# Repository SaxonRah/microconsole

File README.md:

# MicroConsole

MicroConsole is a small cross-platform console integration project built around
[MicroRender](third_party/microrender) for graphics and
[MicroWave](third_party/microwave) for audio.

The repository does **not** fork either engine. MicroRender and MicroWave remain
pinned Git submodules; MicroConsole owns the platform glue that runs them at the
same time and is the place where console-level services can be added later.

The current program is deliberately a stress/integration demo rather than a
finished game runtime: the deterministic MicroRender stress scene runs
continuously while the MicroWave music demo plays.

## Validated baseline

As of **2026-09-01**, the combined integration is working on all three targets:

| Target | Graphics | Audio | Validated result |
| --- | --- | --- | --- |
| Pico 2 / Pimoroni Pico Plus 2 | 320x240 RGB565 ILI9341, 1024-sprite 8-row lace | 32 kHz I2S | ~110 FPS with continuous audio |
| 16-bit DOS | 320x240 RGB565 logical image -> RGB332 Mode X | 11.025 kHz Sound Blaster 8-bit DMA | ~92 FPS with continuous audio |
| Raylib desktop | 320x240 RGB565, 1024-sprite 8-row lace | 32 kHz Raylib `AudioStream` | graphics + audio verified working |

The DOS reference/diagnostic builds measure 97 FPS (`MCREF`), 94 FPS
(`MCGFX`), and 95 FPS (`MCDEMO /noaudio`) for the same 1024-sprite workload,
which puts the combined 92 FPS result within a few percent of the renderer-only
baseline.

See [docs/VALIDATION.md](docs/VALIDATION.md) for the exact test commands and
what each number means.

## Quick start

Clone the repository, then initialize the pinned dependencies:

```powershell
.\mc.bat deps
```

### Raylib

```powershell
.\mc.bat build raylib
.\mc.bat run raylib
```

Press **Space** to trigger the MicroWave synth SFX while the music demo is
playing.

### DOS

```powershell
.\mc.bat build dos
.\mc.bat run dos /sprites 1024 /frames 2100
```

The DOS build also produces two renderer-parity diagnostics:

```powershell
.\mc.bat run dosref /sprites 1024 /frames 2100
.\mc.bat run dosgfx /sprites 1024 /frames 2100
.\mc.bat run dos /sprites 1024 /frames 2100 /noaudio
```

### Pico 2

```powershell
.\mc.bat build pico max98357a
.\mc.bat run pico max98357a swd
```

Other audio presets:

```powershell
.\mc.bat build pico pcm5102a
.\mc.bat build pico ns4168
```

Flash methods are `swd` (default), `picotool`, and `manual` BOOTSEL copy.

## Dependency pins

MicroConsole is validated against these exact engine revisions:

- MicroRender: `61d8d875cbdf605edaa2b6ca2f2e5739b80ee61d`
- MicroWave: `2492cc4026a5e3cdebbac6dea91dbc9eabe88d91`

`mc.bat deps` initializes those two gitlinks, checks out the pinned commits, and
initializes the single Raylib checkout nested under MicroRender. It can also
repair the specific case where `.gitmodules` survived a copied/archive tree but
the two mode-160000 gitlink entries did not.

## What belongs here

MicroConsole owns integration and platform policy:

- selecting/building the two engines together;
- display/audio device setup;
- platform scheduling between rendering, presentation, and mixing;
- console-facing input/storage/save/power services as they are added;
- target-specific diagnostics and performance regression tests.

MicroConsole does **not** own the renderer or mixer implementation. Changes that
are generally useful to graphics belong in MicroRender; changes generally useful
to audio belong in MicroWave.

## Repository layout

```text
microconsole/
  mc.bat                  one build/run/dependency entry point
  CMakeLists.txt          Raylib combined target
  pico/                   Pico SDK project and audio-device presets
  scripts/                build, run, flash/tooling helpers
  src/
    dos/                   DOS combined frontend + Sound Blaster transport
    pico/                  RP2350 combined frontend
    raylib/                desktop combined frontend
  docs/
    ARCHITECTURE.md        ownership, data flow, platform resource model
    BUILDING.md            prerequisites and exact build/run options
    VALIDATION.md          measured baseline and regression procedure
    TROUBLESHOOTING.md     failures already encountered and their causes
  CONSOLE_HARDWARE.md      path from integration demo to handheld hardware
  third_party/
    microrender/           pinned git submodule
    microwave/             pinned git submodule
```

## Documentation

- [Building and running](docs/BUILDING.md)
- [Architecture](docs/ARCHITECTURE.md)
- [Validated performance](docs/VALIDATION.md)
- [Troubleshooting](docs/TROUBLESHOOTING.md)
- [Handheld hardware roadmap](CONSOLE_HARDWARE.md)

## Current scope

The integration layer is now validated. The next console services are expected
to be input, storage/filesystem, saves/settings, power management, and a launcher
or game packaging policy. Those should remain platform services so game code
need not know whether data came from FAT on an SD card, a host directory, or an
embedded image.

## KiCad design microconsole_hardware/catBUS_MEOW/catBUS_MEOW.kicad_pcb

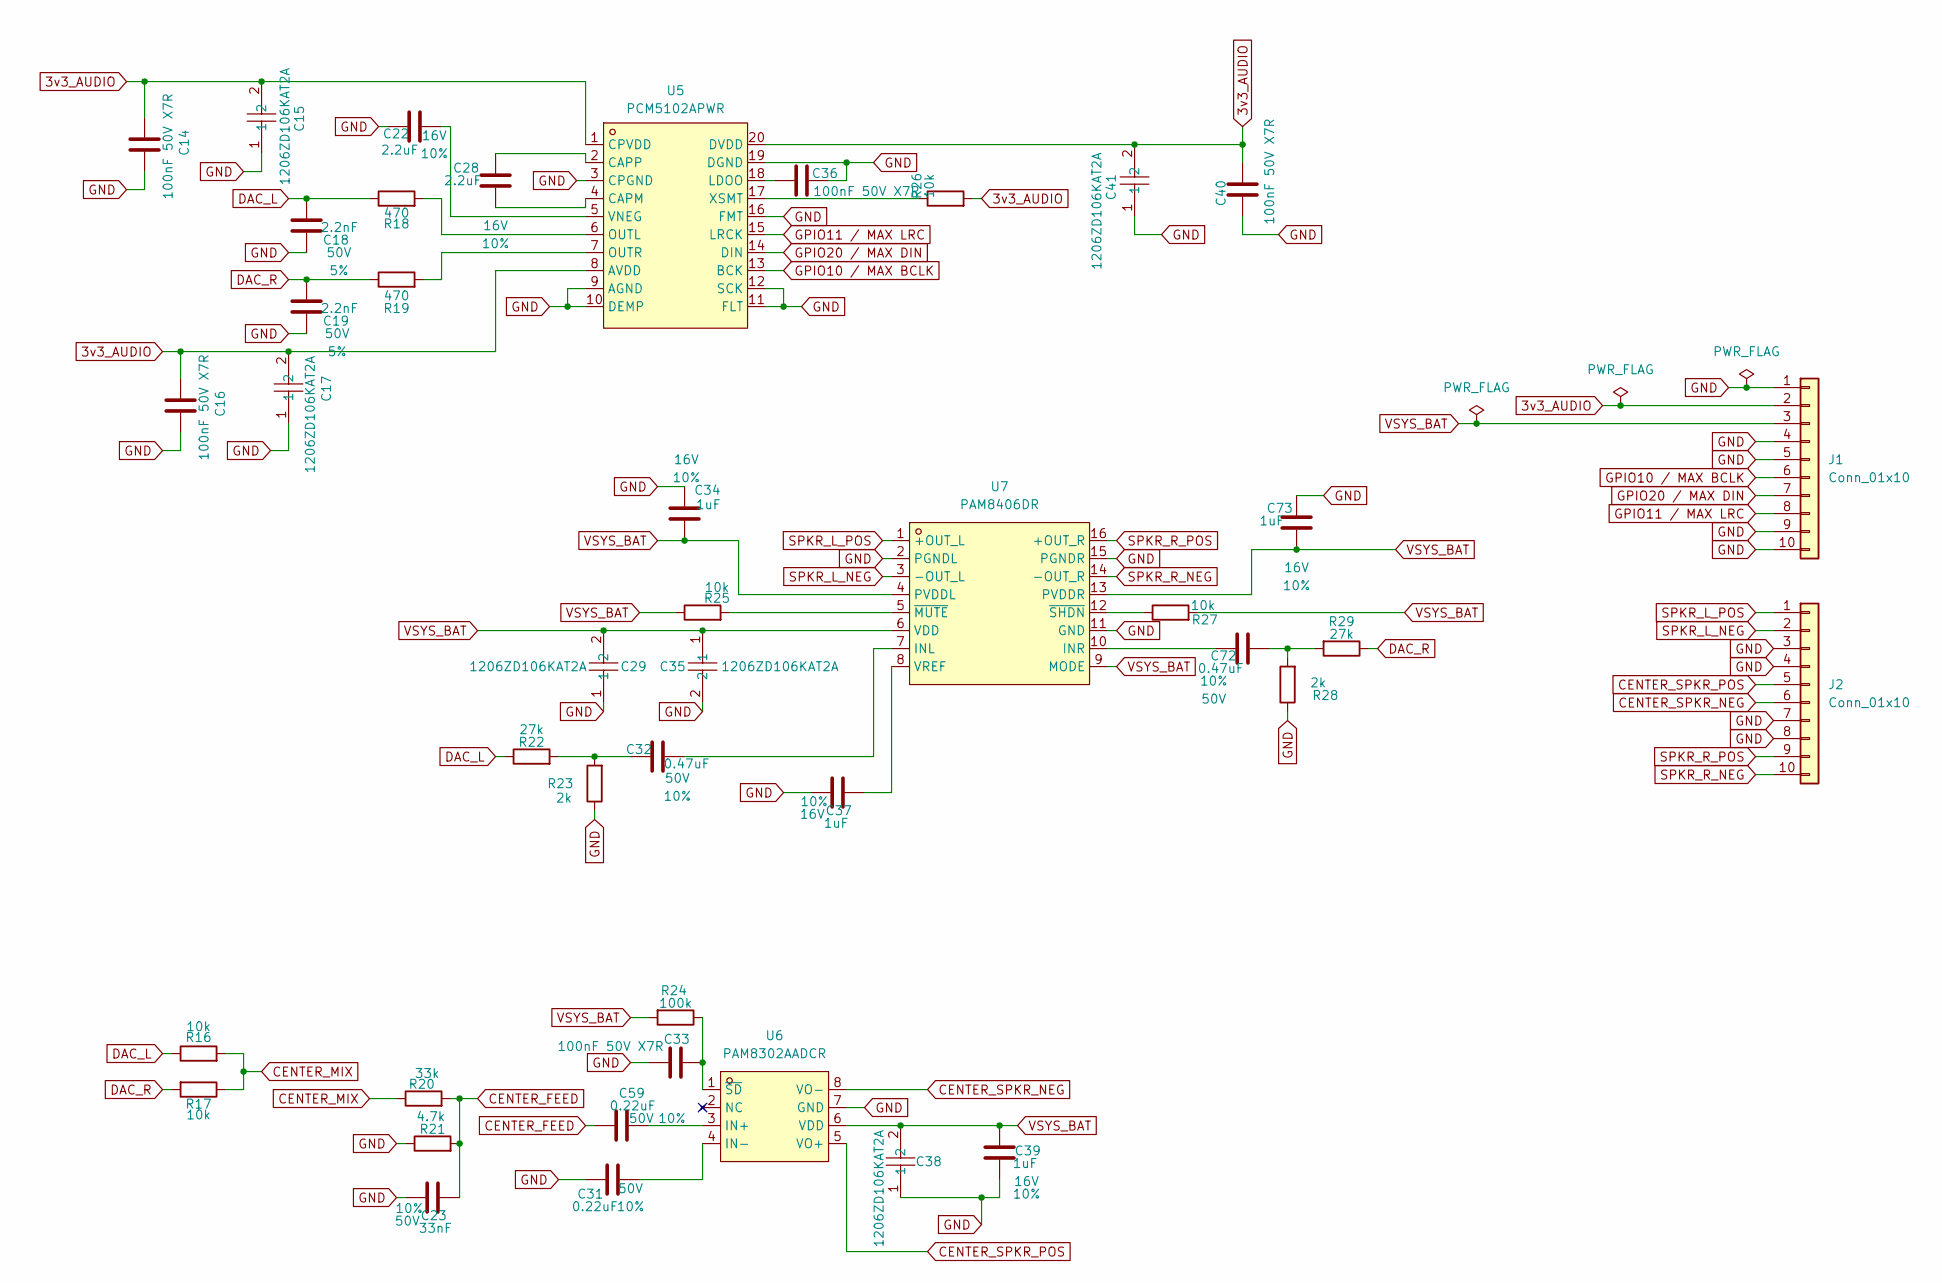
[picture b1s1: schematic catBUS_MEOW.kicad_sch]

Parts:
C14, C16, C33, C36, C40: 100nF 50V X7R; C_0805_2012Metric_KEMET_IPC-B; Tolerance 10%; Voltage 50V; MPN C0805C104K5RAC7210
C15, C17, C29, C35, C38, C41: 1206ZD106KAT2A; C1206; Tolerance 10%; Voltage 10V; MPN 1206ZD106KAT2A; LCSC Part C597553
C18, C19: 2.2nF; C_0805_2012Metric; Voltage 50V; Tolerance 5%; MPN C0805C222J5GECTU
C22, C28: 2.2uF; C_0805_2012Metric; Voltage 16V; Tolerance 10%; MPN GRM21BR71C225KA12L
C23: 33nF; C_0805_2012Metric; Voltage 50V; Tolerance 10%; MPN C0805C333K5RECAUTO
C31, C59: 0.22uF; C_0805_2012Metric; Voltage 50V; Tolerance 10%; MPN C2012X7R1H224K125AA
C32, C72: 0.47uF; C_0805_2012Metric; Voltage 50V; Tolerance 10%; MPN C2012X7R1H474K125AB
C34, C37, C39, C73: 1uF; C_0805_2012Metric; Voltage 16V; Tolerance 10%; MPN GRM21BR71C105KA01L
J1, J2: Conn_01x10; 1x10_P2.54mm
R16, R17, R25, R26, R27: 10k; R_0603_1608Metric; Tolerance 1%; MPN RC0603FR-0710KL
R18, R19: 470; R_0603_1608Metric; Tolerance 1%; MPN RC0603FR-07470RL
R20: 33k; R_0603_1608Metric; Tolerance 1%; MPN RC0603FR-0733KL
R21: 4.7k; R_0603_1608Metric; Tolerance 1%; MPN RC0603FR-074K7L
R22, R29: 27k; R_0603_1608Metric; Tolerance 1%; MPN RC0603FR-0727KL
R23, R28: 2k; R_0603_1608Metric; Tolerance 1%; MPN RC0603FR-072KL
R24: 100k; R_0603_1608Metric; Tolerance 1%; MPN RC0603FR-07100KL
U5: PCM5102APWR; TSSOP-20_L6.5-W4.4-P0.65-LS6.4-BL; MPN PCM5102APWR; LCSC Part C107671
U6: PAM8302AADCR; SOP-8_L4.9-W3.9-P1.27-LS6.0-BL; MPN PAM8302AADCR; LCSC Part C112137
U7: PAM8406DR; SOIC-16_L9.9-W3.9-P1.27-LS6.0-BL; MPN PAM8406DR; LCSC Part C86270

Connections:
3v3_AUDIO: C14.2, C15.2, C16.2, C17.2, C40.2, C41.2, J1.2, R26.2, U5.1 (CPVDD), U5.8 (AVDD), U5.20 (DVDD)
CENTER_FEED: C23.1, C59.1, R20.2, R21.2
CENTER_MIX: R16.2, R17.1, R20.1
CENTER_SPKR_NEG: J2.6, U6.8 (VO-)
CENTER_SPKR_POS: J2.5, U6.5 (VO+)
DAC_L: C18.1, R16.1, R18.1, R22.1
DAC_R: C19.1, R17.2, R19.1, R29.1
GND: C14.1, C15.1, C16.1, C17.1, C18.2, C19.2, C22.2, C23.2, C29.1, C31.2, C33.1, C34.1, C35.2, C36.1, C37.2, C38.1, C39.2, C40.1, C41.1, C73.1, J1.1, J1.4, J1.5, J1.9, J1.10, J2.3, J2.4, J2.7, J2.8, R21.1, R23.1, R28.1, U5.3 (CPGND), U5.9 (AGND), U5.10 (DEMP), U5.11 (FLT), U5.12 (SCK), U5.16 (FMT), U5.19 (DGND), U6.7 (GND), U7.2 (PGNDL), U7.11 (GND), U7.15 (PGNDR)
GPIO10 / MAX BCLK: J1.6, U5.13 (BCK)
GPIO11 / MAX LRC: J1.8, U5.15 (LRCK)
GPIO20 / MAX DIN: J1.7, U5.14 (DIN)
unnamed: C32.2, R22.2, R23.2
unnamed: C72.2, R28.2, R29.2
unnamed: C28.2, U5.4 (CAPM)
unnamed: C28.1, U5.2 (CAPP)
unnamed: C36.2, U5.18 (LDOO)
unnamed: R18.2, U5.6 (OUTL)
unnamed: R19.2, U5.7 (OUTR)
unnamed: C22.1, U5.5 (VNEG)
unnamed: R26.1, U5.17 (XSMT)
unnamed: C59.2, U6.3 (IN+)
unnamed: C31.1, U6.4 (IN-)
unnamed: C33.2, R24.1, U6.1 (~SD)
unnamed: C32.1, U7.7 (INL)
unnamed: C72.1, U7.10 (INR)
unnamed: C37.1, U7.8 (VREF)
unnamed: R25.2, U7.5 (~MUTE)
unnamed: R27.1, U7.12 (~SHDN)
SPKR_L_NEG: J2.2, U7.3 (-OUT_L)
SPKR_L_POS: J2.1, U7.1 (+OUT_L)
SPKR_R_NEG: J2.10, U7.14 (-OUT_R)
SPKR_R_POS: J2.9, U7.16 (+OUT_R)
VSYS_BAT: C29.2, C34.2, C35.1, C38.2, C39.1, C73.2, J1.3, R24.2, R25.1, R27.2, U6.6 (VDD), U7.4 (PVDDL), U7.6 (VDD), U7.9 (MODE), U7.13 (PVDDR)

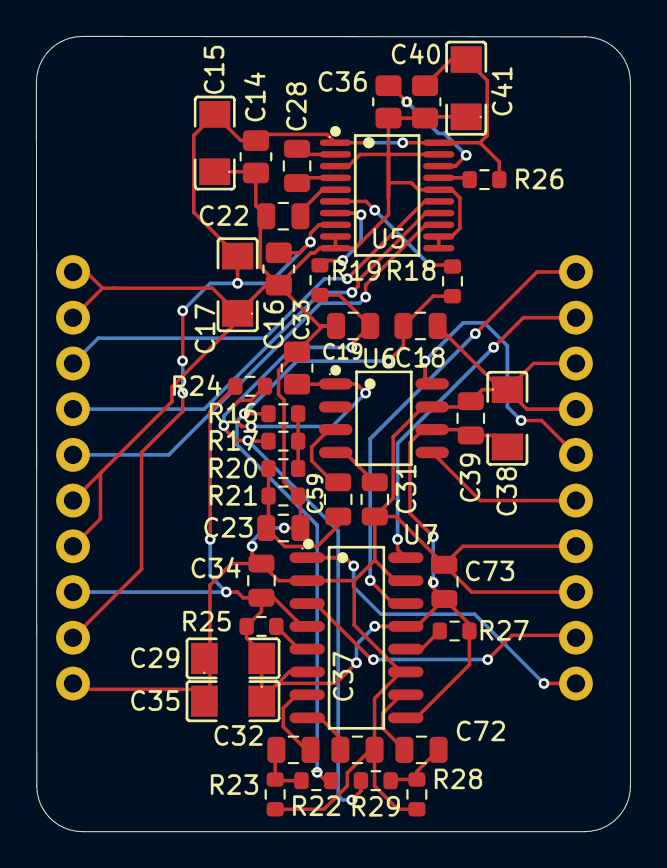
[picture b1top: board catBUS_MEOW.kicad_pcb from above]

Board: 2 copper layers, 33.0 x 44.2 mm, 43 parts (0 on the bottom side), 33 nets.

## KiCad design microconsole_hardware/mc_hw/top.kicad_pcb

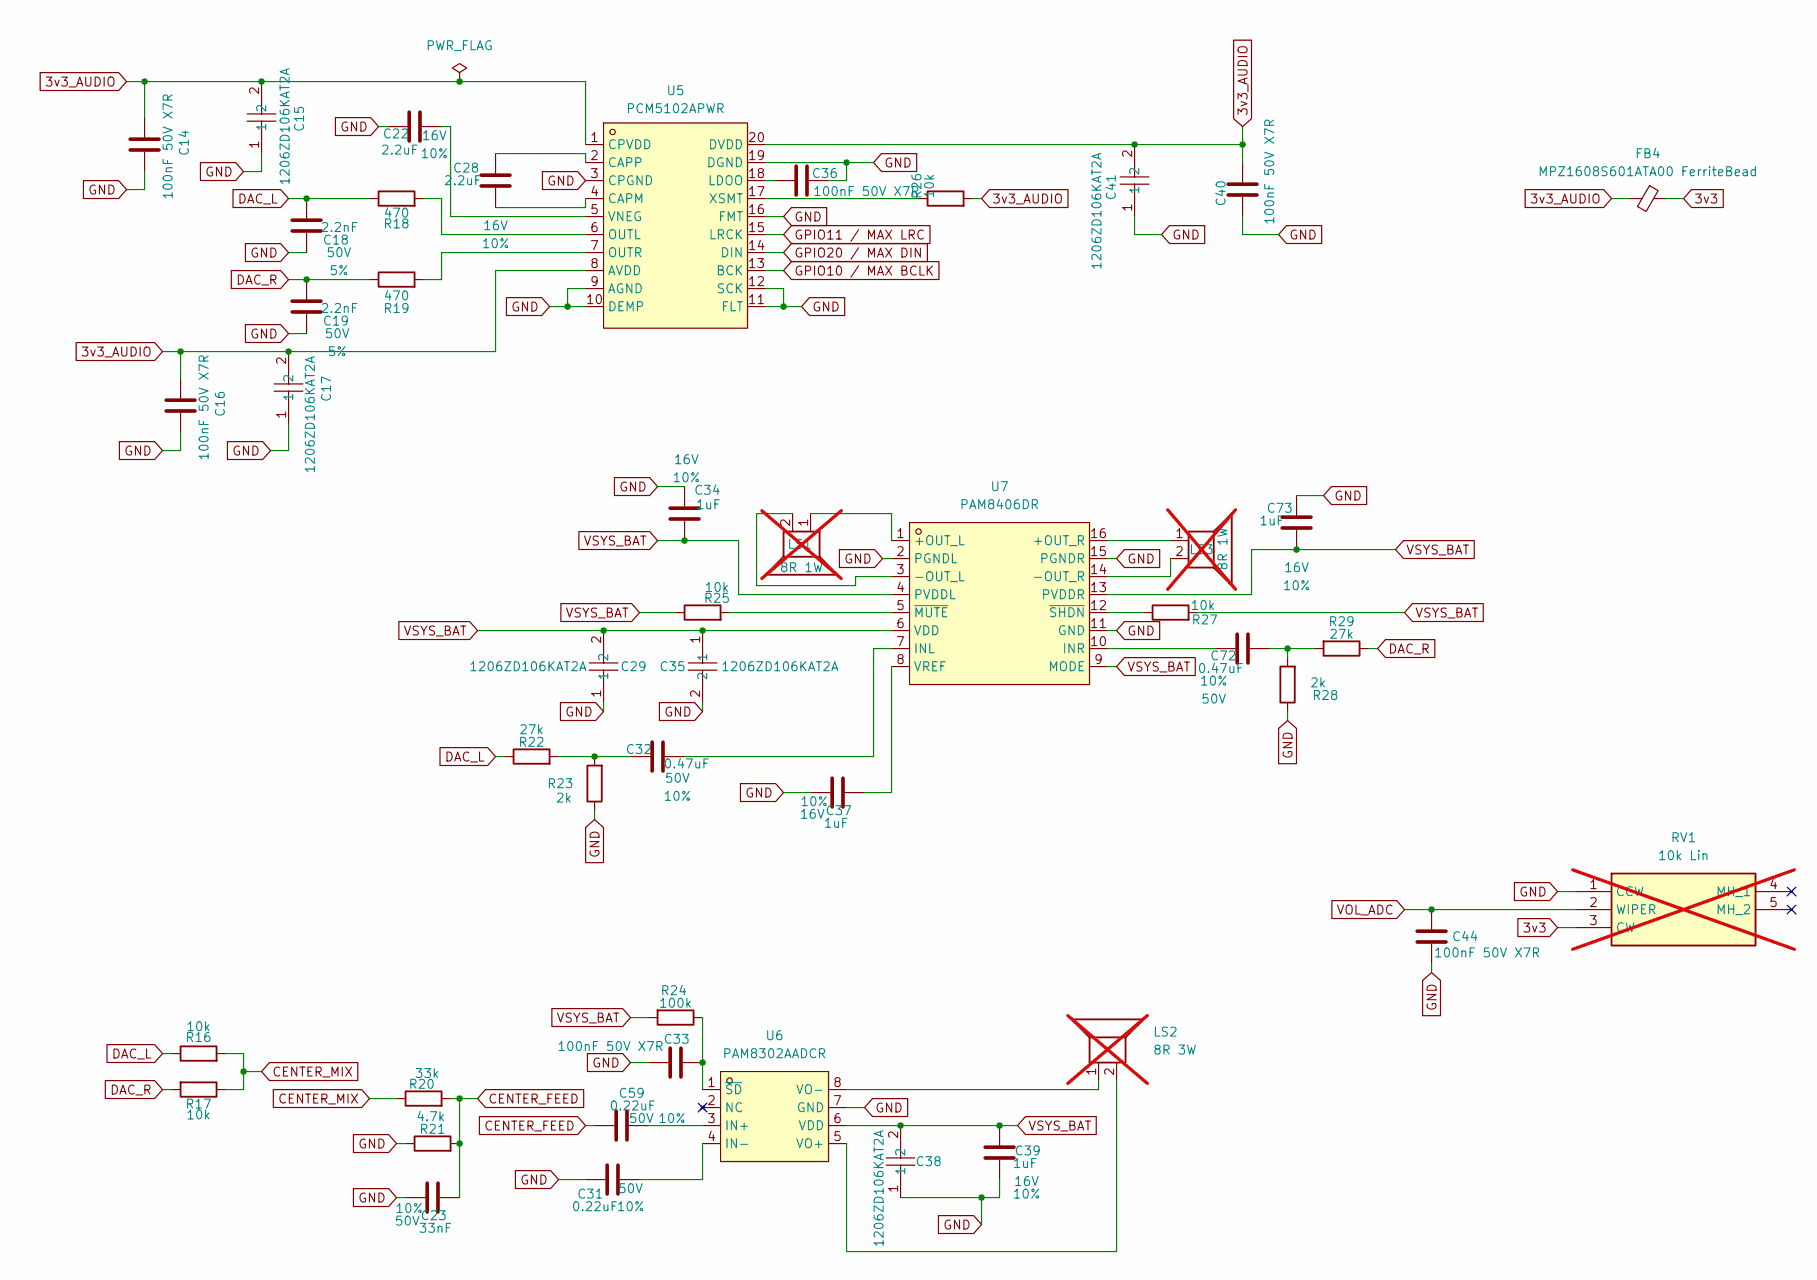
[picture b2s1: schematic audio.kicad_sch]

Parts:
C14, C16, C33, C36, C40, C44: 100nF 50V X7R; C_0805_2012Metric_KEMET_IPC-B; Tolerance 10%; Voltage 50V; MPN C0805C104K5RAC7210
C15, C17, C29, C35, C38, C41: 1206ZD106KAT2A; C1206; Tolerance 10%; Voltage 10V; MPN 1206ZD106KAT2A; LCSC Part C597553
C18, C19: 2.2nF; C_0805_2012Metric; Voltage 50V; Tolerance 5%; MPN C0805C222J5GECTU
C22, C28: 2.2uF; C_0805_2012Metric; Voltage 16V; Tolerance 10%; MPN GRM21BR71C225KA12L
C23: 33nF; C_0805_2012Metric; Voltage 50V; Tolerance 10%; MPN C0805C333K5RECAUTO
C31, C59: 0.22uF; C_0805_2012Metric; Voltage 50V; Tolerance 10%; MPN C2012X7R1H224K125AA
C32, C72: 0.47uF; C_0805_2012Metric; Voltage 50V; Tolerance 10%; MPN C2012X7R1H474K125AB
C34, C37, C39, C73: 1uF; C_0805_2012Metric; Voltage 16V; Tolerance 10%; MPN GRM21BR71C105KA01L
FB4: MPZ1608S601ATA00 FerriteBead; L_0603_1608Metric_Pad1.05x0.95mm_HandSolder; MPN MPZ1608S601ATA00
LS1, LS3: 8R 1W; Molex_PicoBlade_53047-0210_1x02_P1.25mm_Vertical; MPN AS02008MR-2-LWC30; not fitted
LS2: 8R 3W; Speaker_WirePads_1x02_P3.50mm_D1.0mm; MPN AS03208AS-HT; not fitted
R16, R17, R25, R26, R27: 10k; R_0603_1608Metric; Tolerance 1%; MPN RC0603FR-0710KL
R18, R19: 470; R_0603_1608Metric; Tolerance 1%; MPN RC0603FR-07470RL
R20: 33k; R_0603_1608Metric; Tolerance 1%; MPN RC0603FR-0733KL
R21: 4.7k; R_0603_1608Metric; Tolerance 1%; MPN RC0603FR-074K7L
R22, R29: 27k; R_0603_1608Metric; Tolerance 1%; MPN RC0603FR-0727KL
R23, R28: 2k; R_0603_1608Metric; Tolerance 1%; MPN RC0603FR-072KL
R24: 100k; R_0603_1608Metric; Tolerance 1%; MPN RC0603FR-07100KL
RV1: 10k Lin; PTV09A2015FB103; Tolerance 1%; Mouser Part Number 652-PTV09A-2015FB103; not fitted
U5: PCM5102APWR; TSSOP-20_L6.5-W4.4-P0.65-LS6.4-BL; MPN PCM5102APWR; LCSC Part C107671
U6: PAM8302AADCR; SOP-8_L4.9-W3.9-P1.27-LS6.0-BL; MPN PAM8302AADCR; LCSC Part C112137
U7: PAM8406DR; SOIC-16_L9.9-W3.9-P1.27-LS6.0-BL; MPN PAM8406DR; LCSC Part C86270

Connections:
3v3: FB4.1, RV1.3 (CW); also elsewhere on the board
3v3_AUDIO: C14.2, C15.2, C16.2, C17.2, C40.2, C41.2, FB4.2, R26.2, U5.1 (CPVDD), U5.8 (AVDD), U5.20 (DVDD)
CENTER_FEED: C23.1, C59.1, R20.2, R21.2
CENTER_MIX: R16.2, R17.1, R20.1
DAC_L: C18.1, R16.1, R18.1, R22.1
DAC_R: C19.1, R17.2, R19.1, R29.1
GND: C14.1, C15.1, C16.1, C17.1, C18.2, C19.2, C22.2, C23.2, C29.1, C31.2, C33.1, C34.1, C35.2, C36.1, C37.2, C38.1, C39.2, C40.1, C41.1, C44.1, C73.1, R21.1, R23.1, R28.1, RV1.1 (CCW), U5.3 (CPGND), U5.9 (AGND), U5.10 (DEMP), U5.11 (FLT), U5.12 (SCK), U5.16 (FMT), U5.19 (DGND), U6.7 (GND), U7.2 (PGNDL), U7.11 (GND), U7.15 (PGNDR); also elsewhere on the board
GPIO10 / MAX BCLK: U5.13 (BCK); also elsewhere on the board
GPIO11 / MAX LRC: U5.15 (LRCK); also elsewhere on the board
GPIO20 / MAX DIN: U5.14 (DIN); also elsewhere on the board
unnamed: C32.2, R22.2, R23.2
unnamed: C72.2, R28.2, R29.2
unnamed: LS1.1 (+_(red)), U7.1 (+OUT_L)
unnamed: LS1.2 (-_(black)), U7.3 (-OUT_L)
unnamed: LS2.1 (+), U6.8 (VO-)
unnamed: LS2.2 (-), U6.5 (VO+)
unnamed: LS3.1 (+_(red)), U7.16 (+OUT_R)
unnamed: LS3.2 (-_(black)), U7.14 (-OUT_R)
unnamed: C28.2, U5.4 (CAPM)
unnamed: C28.1, U5.2 (CAPP)
unnamed: C36.2, U5.18 (LDOO)
unnamed: R18.2, U5.6 (OUTL)
unnamed: R19.2, U5.7 (OUTR)
unnamed: C22.1, U5.5 (VNEG)
unnamed: R26.1, U5.17 (XSMT)
unnamed: C59.2, U6.3 (IN+)
unnamed: C31.1, U6.4 (IN-)
unnamed: C33.2, R24.1, U6.1 (~SD)
unnamed: C32.1, U7.7 (INL)
unnamed: C72.1, U7.10 (INR)
unnamed: C37.1, U7.8 (VREF)
unnamed: R25.2, U7.5 (~MUTE)
unnamed: R27.1, U7.12 (~SHDN)
VOL_ADC: C44.2, RV1.2 (WIPER); also elsewhere on the board

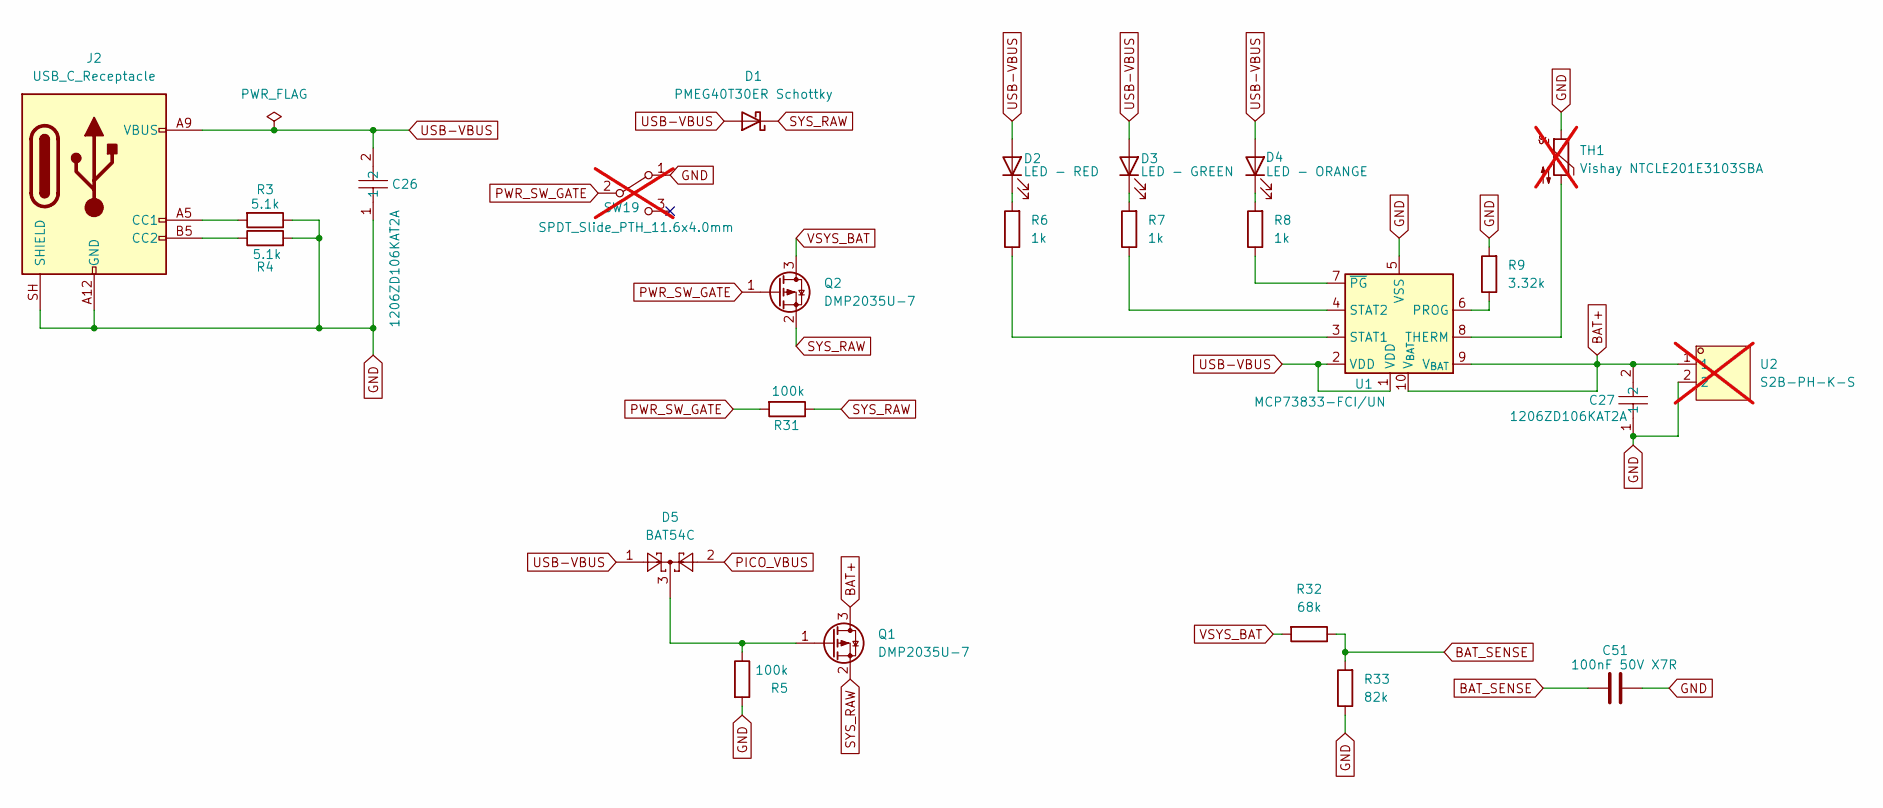
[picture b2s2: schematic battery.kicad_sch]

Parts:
C26, C27: 1206ZD106KAT2A; C1206; Tolerance 10%; Voltage 10V; MPN 1206ZD106KAT2A; LCSC Part C597553
C51: 100nF 50V X7R; C_0805_2012Metric_KEMET_IPC-B; Tolerance 10%; Voltage 50V; MPN C0805C104K5RAC7210
D1: PMEG40T30ER Schottky; Nexperia_CFP3_SOD-123W; MPN PMEG40T30ERX
D2: LED - RED; LED_0603_1608Metric_Pad1.05x0.95mm_HandSolder; MPN LTST-C190KRKT
D3: LED - GREEN; LED_0603_1608Metric_Pad1.05x0.95mm_HandSolder; MPN LTST-C190KGKT
D4: LED - ORANGE; LED_0603_1608Metric_Pad1.05x0.95mm_HandSolder; MPN LTST-C190KFKT
D5: BAT54C; SOT-23; MPN BAT54C-7-F
J2: USB_C_Receptacle; USB_C_Receptacle_HCTL_HC-TYPE-C-16P-01A
Q1, Q2: DMP2035U-7; SOT-23; MPN DMP2035U-7
R3, R4: 5.1k; R_0603_1608Metric; Tolerance 1%; MPN RC0603FR-075K1L
R5, R31: 100k; R_0603_1608Metric; Tolerance 1%; MPN RC0603FR-07100KL
R6, R7, R8: 1k; R_0603_1608Metric; Tolerance 1%; MPN RC0603FR-071KL
R9: 3.32k; R_0603_1608Metric; Tolerance 1%; MPN RC0603FR-073K32L
R32: 68k; R_0603_1608Metric; Tolerance 1%; MPN RC0603FR-0768KL
R33: 82k; R_0603_1608Metric; Tolerance 1%; MPN RC0603FR-0782KL
SW19: SPDT_Slide_PTH_11.6x4.0mm; Slide_SPDT_PTH_11.6x4.0mm; MPN COM-00102; not fitted
TH1: Vishay NTCLE201E3103SBA; PinHeader_1x02_P2.54mm_Vertical; MPN NTCLE201E3103SBA; not fitted
U1: MCP73833-FCI/UN; MSOP-10_3x3mm_P0.5mm; MPN MCP73833-FCI/UN
U2: S2B-PH-K-S; CONN-TH_S2B-PH-K-S-LF-SN; MPN S2B-PH-K-S(LF)(SN); LCSC Part C173752; not fitted

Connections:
BAT+: C27.2, Q1.3 (D), U1.9 (V_{BAT}), U1.10 (V_{BAT}), U2.1
BAT_SENSE: C51.2, R32.1, R33.2; also elsewhere on the board
GND: C26.1, C27.1, C51.1, J2.A1 (GND), J2.A12 (GND), J2.B1 (GND), J2.B12 (GND), J2.SH (SHIELD), R3.1, R4.2, R5.2, R9.2, R33.1, SW19.1 (A), TH1.1, U1.5 (VSS), U2.2; also elsewhere on the board
unnamed: D2.1 (K), R6.2
unnamed: D3.1 (K), R7.2
unnamed: D4.1 (K), R8.2
unnamed: J2.A5 (CC1), R3.2
unnamed: J2.B5 (CC2), R4.1
unnamed: D5.3, Q1.1 (G), R5.1
unnamed: R9.1, U1.6 (PROG)
unnamed: R6.1, U1.3 (STAT1)
unnamed: R7.1, U1.4 (STAT2)
unnamed: TH1.2, U1.8 (THERM)
unnamed: R8.1, U1.7 (~PG)
PWR_SW_GATE: Q2.1 (G), R31.2, SW19.2 (B)
SYS_RAW: D1.1 (K), Q1.2 (S), Q2.2 (S), R31.1
USB-VBUS: C26.2, D1.2 (A), D2.2 (A), D3.2 (A), D4.2 (A), D5.1, J2.A4 (VBUS), J2.A9 (VBUS), J2.B4 (VBUS), J2.B9 (VBUS), U1.1 (VDD), U1.2 (VDD)

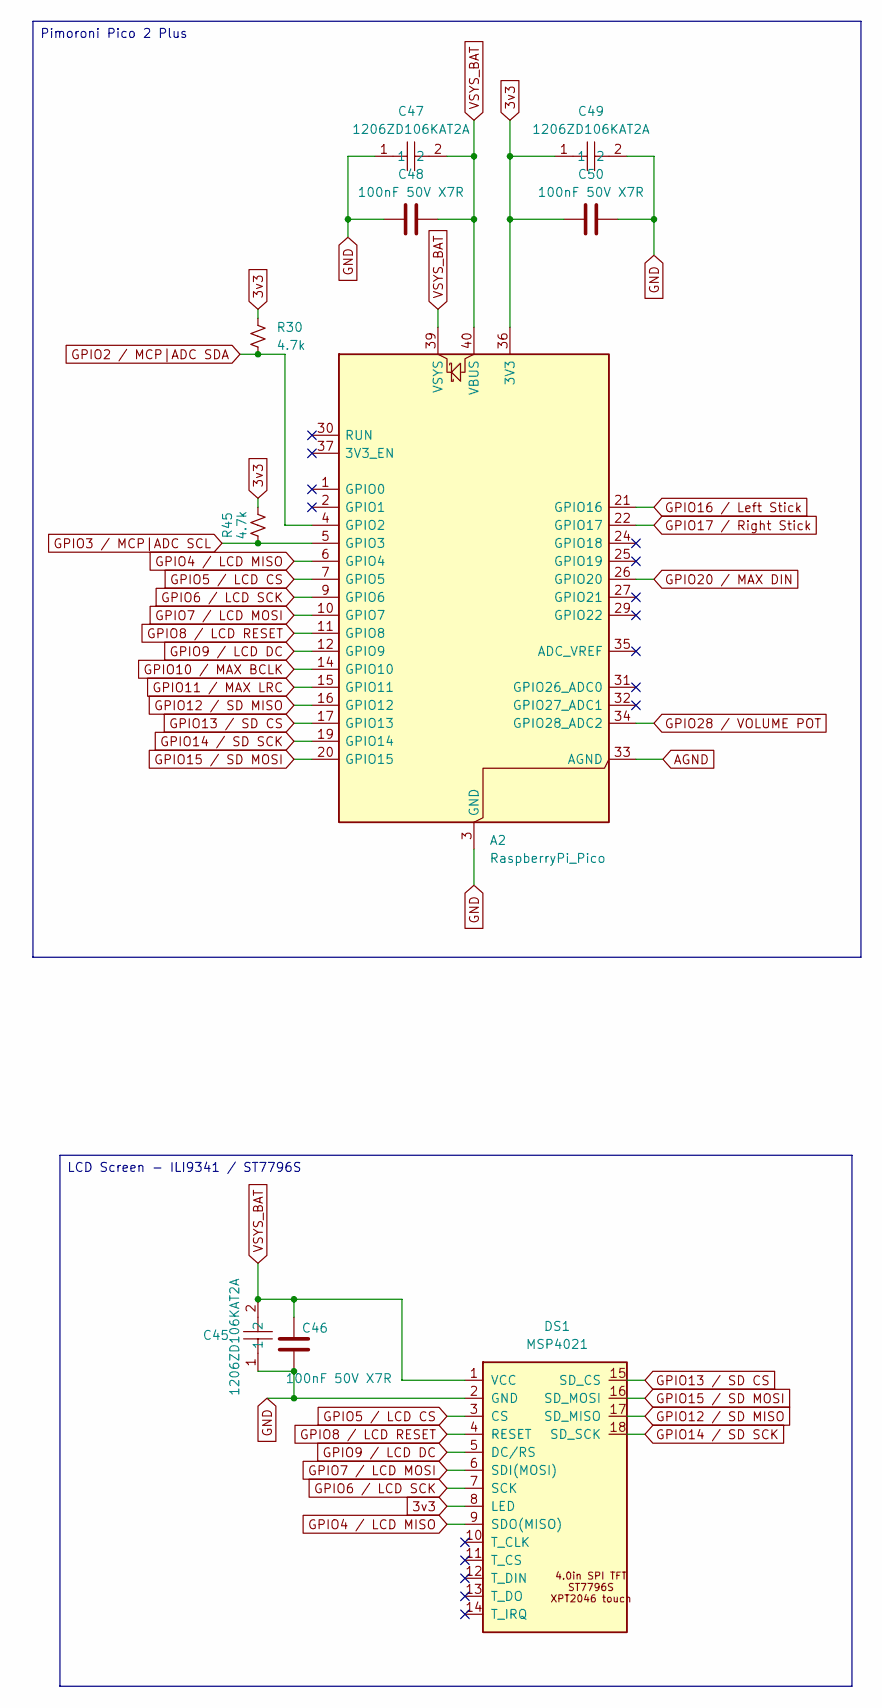
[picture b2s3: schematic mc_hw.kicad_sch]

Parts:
A2: RaspberryPi_Pico; RaspberryPi_Pico_Common_Unspecified
C45, C47, C49: 1206ZD106KAT2A; C1206; MPN 1206ZD106KAT2A; LCSC Part C597553
C46, C48, C50: 100nF 50V X7R; C_0805_2012Metric_KEMET_IPC-B; MPN C0805C104K5RAC7210
DS1: MSP4021; LCD_MSP4021_4.0in_SPI_ST7796_1x14_P2.54mm
R30, R45: 4.7k; R_0603_1608Metric

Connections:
3v3: A2.36 (3V3), C49.1, C50.1, DS1.8 (LED), R30.1, R45.1; also elsewhere on the board
GND: A2.3 (GND), A2.8 (GND), A2.13 (GND), A2.18 (GND), A2.23 (GND), A2.28 (GND), A2.38 (GND), C45.1, C46.2, C47.1, C48.1, C49.2, C50.2, DS1.2 (GND); also elsewhere on the board
GPIO2 / MCP|ADC SDA: A2.4 (GPIO2), R30.2; also elsewhere on the board
GPIO3 / MCP|ADC SCL: A2.5 (GPIO3), R45.2; also elsewhere on the board
GPIO4 / LCD MISO: A2.6 (GPIO4), DS1.9 (SDO(MISO))
GPIO5 / LCD CS: A2.7 (GPIO5), DS1.3 (CS)
GPIO6 / LCD SCK: A2.9 (GPIO6), DS1.7 (SCK)
GPIO7 / LCD MOSI: A2.10 (GPIO7), DS1.6 (SDI(MOSI))
GPIO8 / LCD RESET: A2.11 (GPIO8), DS1.4 (RESET)
GPIO9 / LCD DC: A2.12 (GPIO9), DS1.5 (DC/RS)
GPIO10 / MAX BCLK: A2.14 (GPIO10); also elsewhere on the board
GPIO11 / MAX LRC: A2.15 (GPIO11); also elsewhere on the board
GPIO12 / SD MISO: A2.16 (GPIO12), DS1.17 (SD_MISO)
GPIO13 / SD CS: A2.17 (GPIO13), DS1.15 (SD_CS)
GPIO14 / SD SCK: A2.19 (GPIO14), DS1.18 (SD_SCK)
GPIO15 / SD MOSI: A2.20 (GPIO15), DS1.16 (SD_MOSI)
GPIO16 / Left Stick: A2.21 (GPIO16); also elsewhere on the board
GPIO17 / Right Stick: A2.22 (GPIO17); also elsewhere on the board
GPIO20 / MAX DIN: A2.26 (GPIO20); also elsewhere on the board

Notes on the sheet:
Pimoroni Pico 2 Plus
LCD Screen - ILI9341 / ST7796S

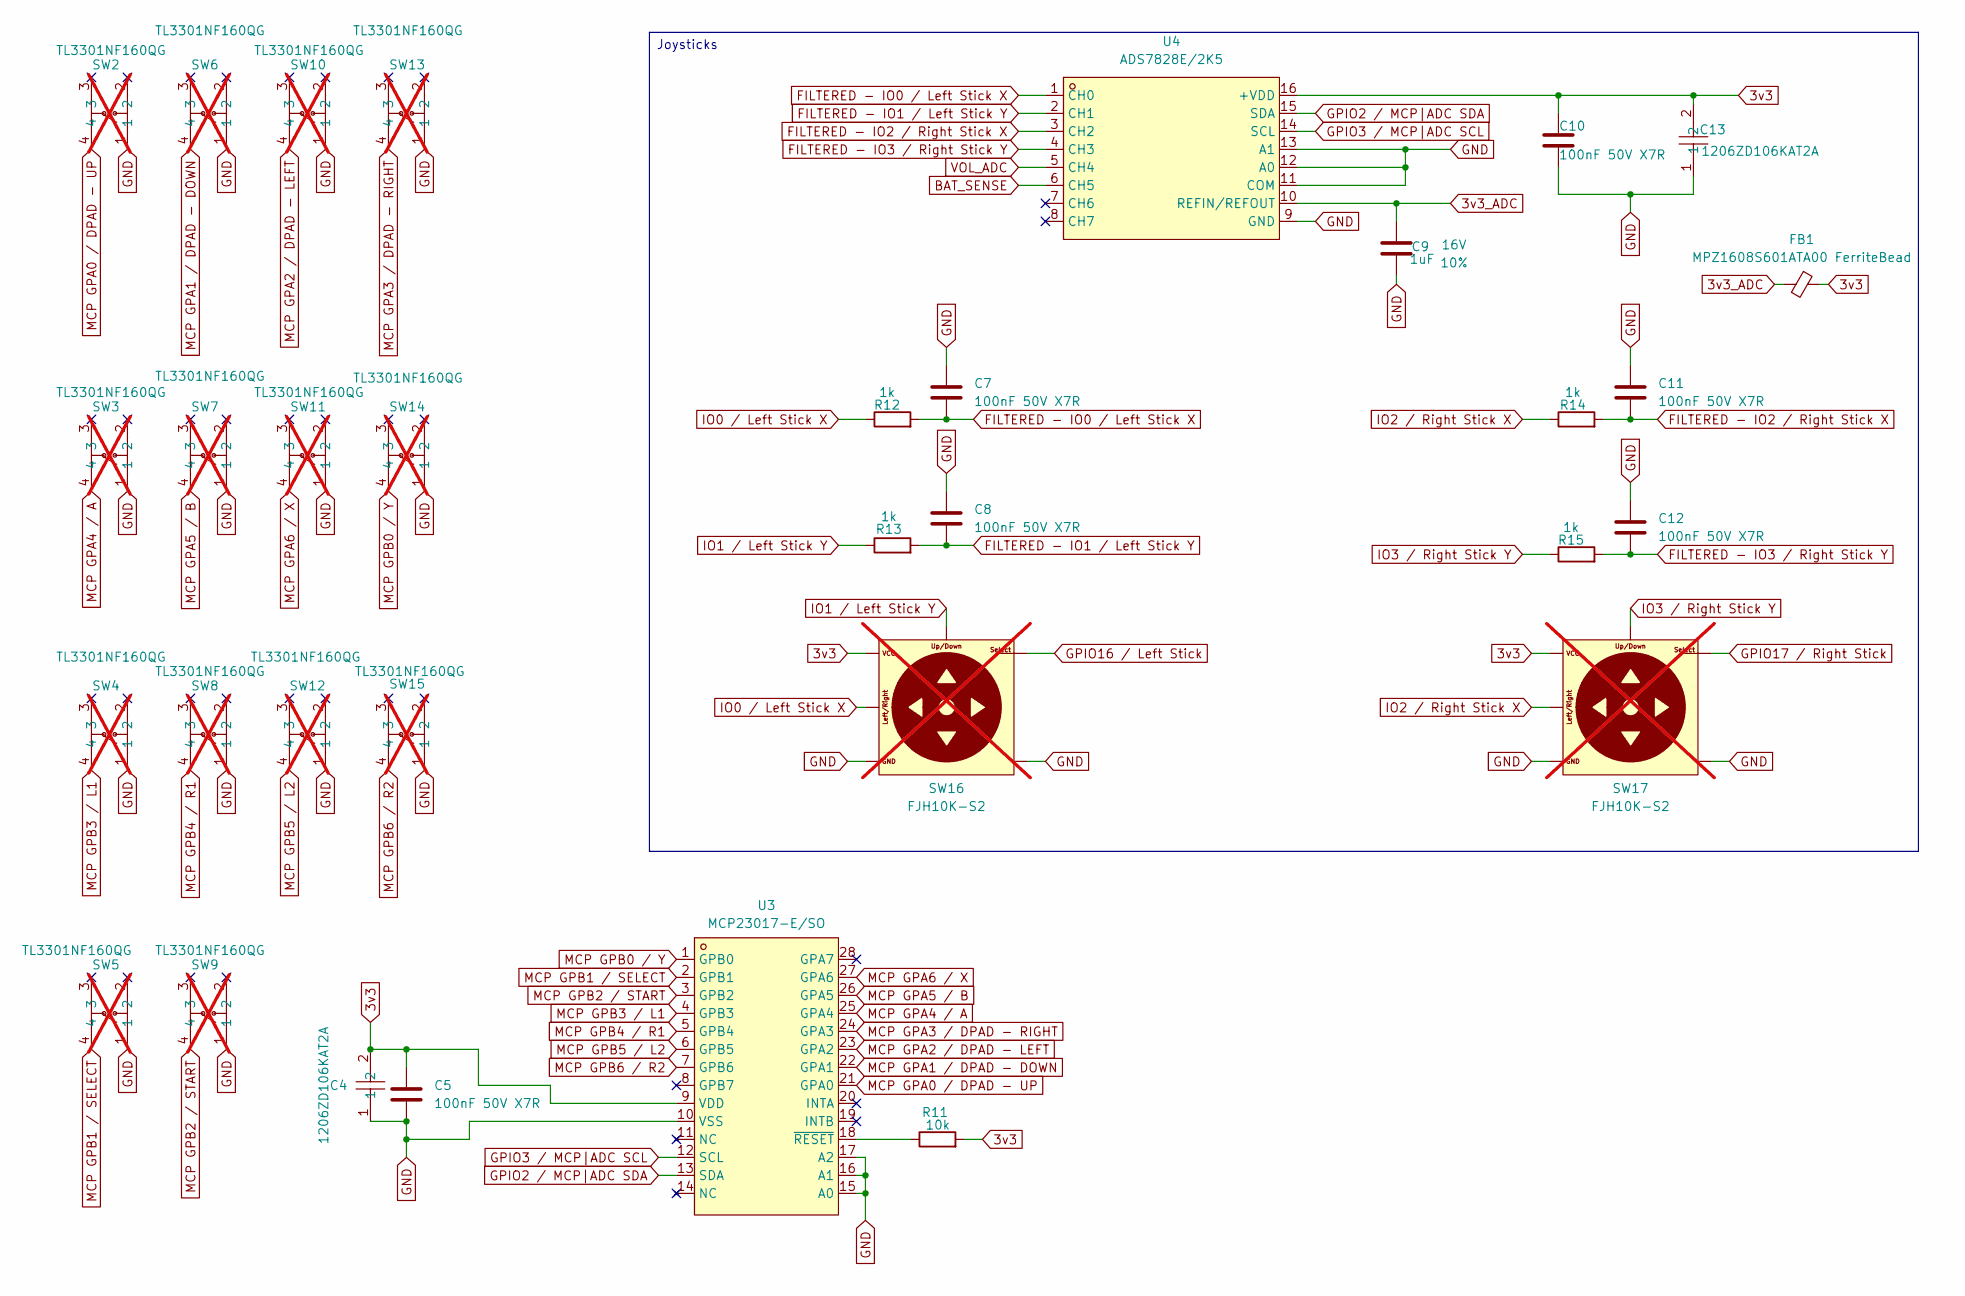
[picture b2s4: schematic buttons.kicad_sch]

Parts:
C4, C13: 1206ZD106KAT2A; C1206; Tolerance 10%; Voltage 10V; MPN 1206ZD106KAT2A; LCSC Part C597553
C5, C7, C8, C10, C11, C12: 100nF 50V X7R; C_0805_2012Metric_KEMET_IPC-B; Tolerance 10%; Voltage 50V; MPN C0805C104K5RAC7210
C9: 1uF; C_0805_2012Metric; Voltage 16V; Tolerance 10%; MPN GRM21BR71C105KA01L
FB1: MPZ1608S601ATA00 FerriteBead; L_0603_1608Metric_Pad1.05x0.95mm_HandSolder; MPN MPZ1608S601ATA00
R11: 10k; R_0603_1608Metric; Tolerance 1%; MPN RC0603FR-0710KL
R12, R13, R14, R15: 1k; R_0603_1608Metric; Tolerance 1%; MPN RC0603FR-071KL
SW2, SW3, SW4, SW5, SW6, SW7, SW8, SW9, SW10, SW11, SW12, SW13, SW14, SW15: TL3301NF160QG; KEY-SMD_4P-L6.0-W6.0-P4.50-LS10.0; MPN TL3301NF160QG; LCSC Part C273526; not fitted
SW16, SW17: FJH10K-S2; GINFULL HallEffect Joystick PTH; MPN FJH10K-S2; not fitted
U3: MCP23017-E/SO; SOIC-28_L18.0-W7.5-P1.27-LS10.3-BL; MPN MCP23017-E/SO; LCSC Part C47023
U4: ADS7828E/2K5; TSSOP-16_L5.0-W4.4-P0.65-LS6.4-BL; MPN ADS7828E/2K5; LCSC Part C701649

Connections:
3v3: C4.2, C5.1, C10.1, C13.2, FB1.1, R11.2, SW16.VCC, SW17.VCC, U3.9 (VDD), U4.16 (+VDD); also elsewhere on the board
3v3_ADC: C9.1, FB1.2, U4.10 (REFIN/REFOUT)
BAT_SENSE: U4.6 (CH5); also elsewhere on the board
FILTERED - IO0 / Left Stick X: C7.2, R12.2, U4.1 (CH0)
FILTERED - IO1 / Left Stick Y: C8.2, R13.2, U4.2 (CH1)
FILTERED - IO2 / Right Stick X: C11.2, R14.2, U4.3 (CH2)
FILTERED - IO3 / Right Stick Y: C12.2, R15.2, U4.4 (CH3)
GND: C4.1, C5.2, C7.1, C8.1, C9.2, C10.2, C11.1, C12.1, C13.1, SW2.1, SW3.1, SW4.1, SW5.1, SW6.1, SW7.1, SW8.1, SW9.1, SW10.1, SW11.1, SW12.1, SW13.1, SW14.1, SW15.1, SW16.GND, SW17.GND, U3.10 (VSS), U3.15 (A0), U3.16 (A1), U3.17 (A2), U4.9 (GND), U4.11 (COM), U4.12 (A0), U4.13 (A1); also elsewhere on the board
GPIO2 / MCP|ADC SDA: U3.13 (SDA), U4.15 (SDA); also elsewhere on the board
GPIO3 / MCP|ADC SCL: U3.12 (SCL), U4.14 (SCL); also elsewhere on the board
GPIO16 / Left Stick: SW16.Select; also elsewhere on the board
GPIO17 / Right Stick: SW17.Select; also elsewhere on the board
IO0 / Left Stick X: R12.1, SW16.Horizontal
IO1 / Left Stick Y: R13.1, SW16.Vertical
IO2 / Right Stick X: R14.1, SW17.Horizontal
IO3 / Right Stick Y: R15.1, SW17.Vertical
MCP GPA0 / DPAD - UP: SW2.4, U3.21 (GPA0)
MCP GPA1 / DPAD - DOWN: SW6.4, U3.22 (GPA1)
MCP GPA2 / DPAD - LEFT: SW10.4, U3.23 (GPA2)
MCP GPA3 / DPAD - RIGHT: SW13.4, U3.24 (GPA3)
MCP GPA4 / A: SW3.4, U3.25 (GPA4)
MCP GPA5 / B: SW7.4, U3.26 (GPA5)
MCP GPA6 / X: SW11.4, U3.27 (GPA6)
MCP GPB0 / Y: SW14.4, U3.1 (GPB0)
MCP GPB1 / SELECT: SW5.4, U3.2 (GPB1)
MCP GPB2 / START: SW9.4, U3.3 (GPB2)
MCP GPB3 / L1: SW4.4, U3.4 (GPB3)
MCP GPB4 / R1: SW8.4, U3.5 (GPB4)
MCP GPB5 / L2: SW12.4, U3.6 (GPB5)
MCP GPB6 / R2: SW15.4, U3.7 (GPB6)
unnamed: R11.1, U3.18 (~RESET)
VOL_ADC: U4.5 (CH4); also elsewhere on the board

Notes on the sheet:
Joysticks

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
